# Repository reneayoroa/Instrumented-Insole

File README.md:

# Instrumented-Insole
KiCAD Design files for an instrumented insole

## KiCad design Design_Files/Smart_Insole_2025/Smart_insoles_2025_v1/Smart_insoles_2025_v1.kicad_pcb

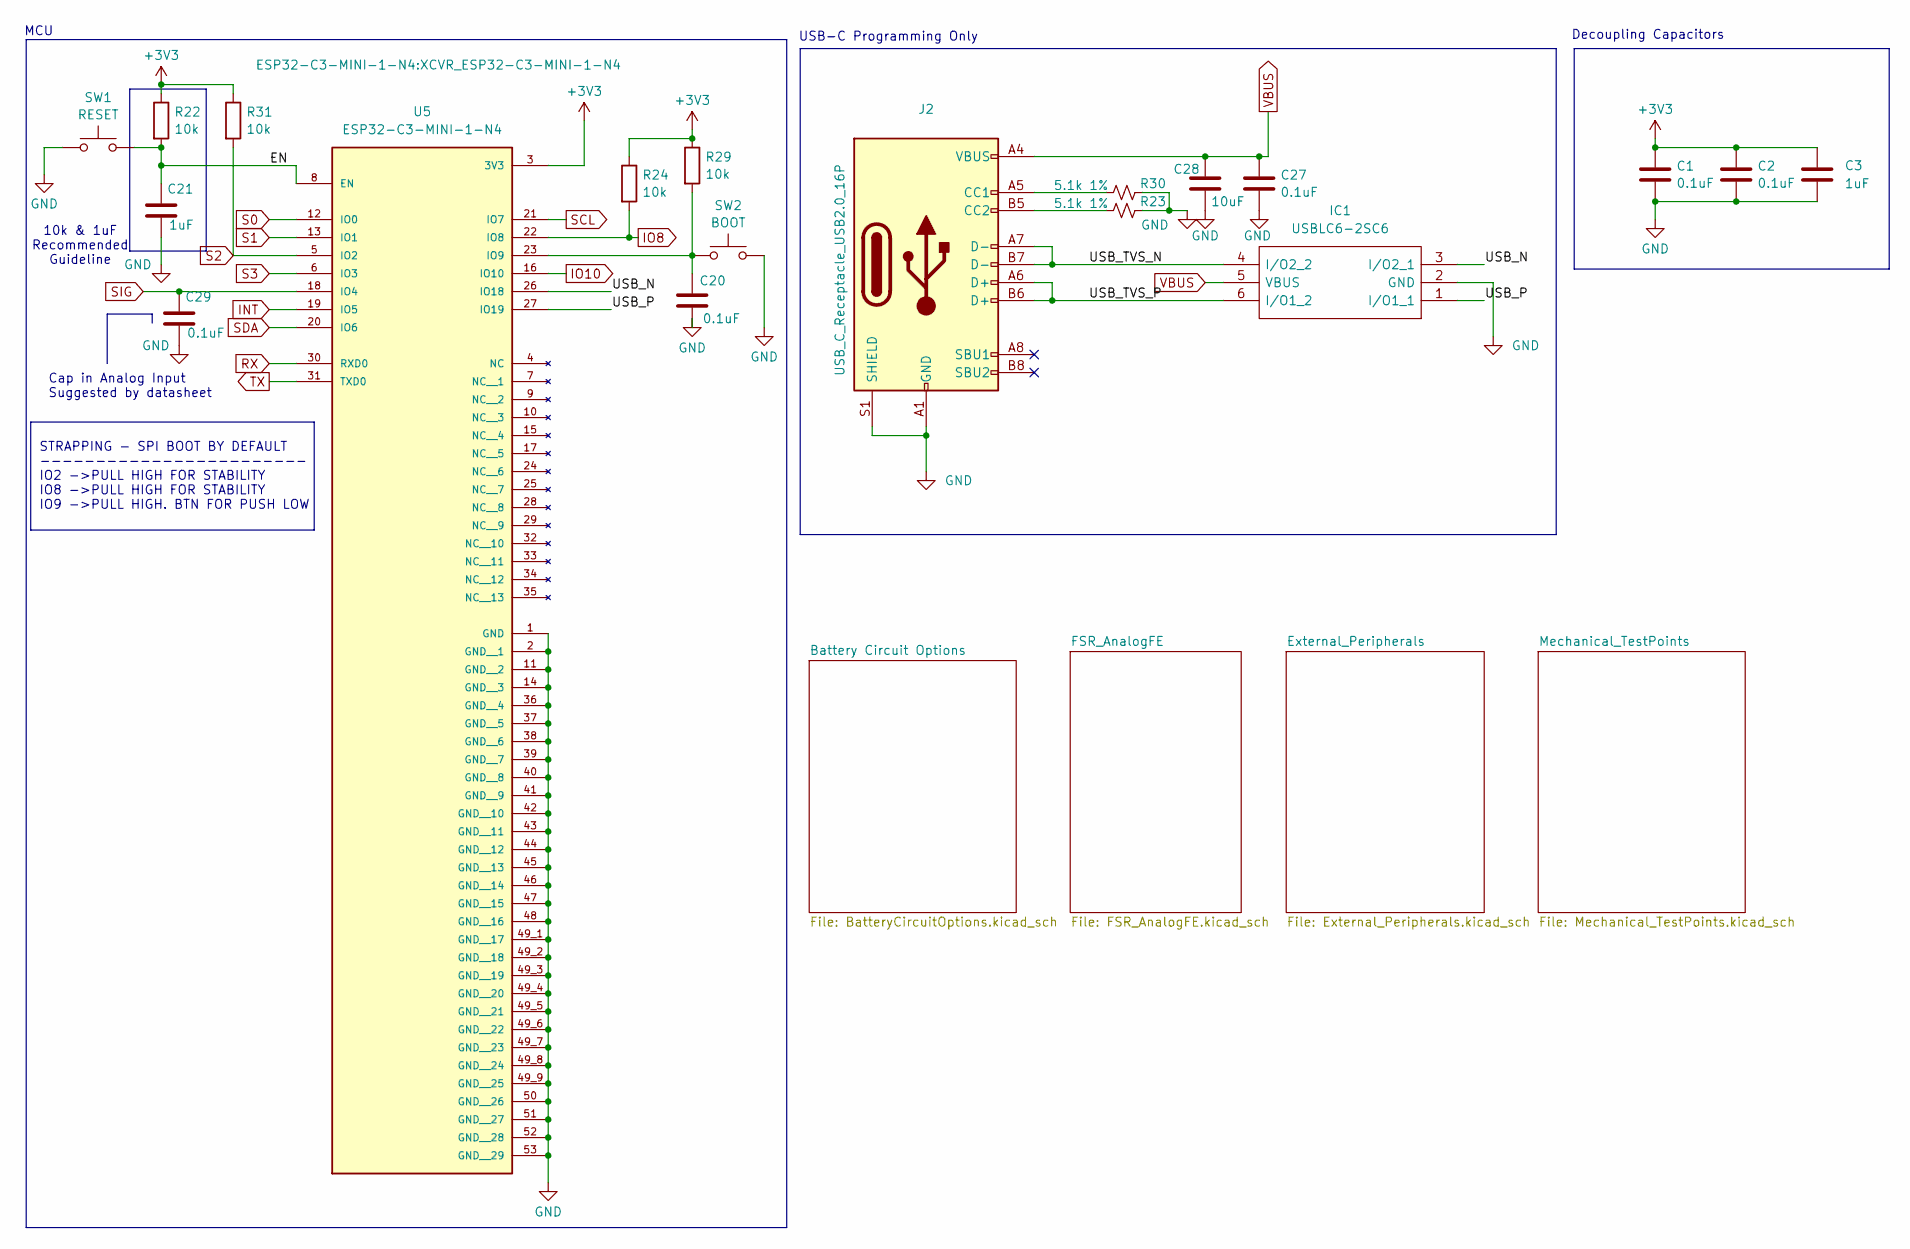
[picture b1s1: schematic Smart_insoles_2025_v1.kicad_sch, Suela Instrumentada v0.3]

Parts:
C1, C2, C20, C27, C29: 0.1uF; C_0805_2012Metric_Pad1.18x1.45mm_HandSolder
C3, C21: 1uF; C_0805_2012Metric_Pad1.18x1.45mm_HandSolder
C28: 10uF; C_0805_2012Metric_Pad1.18x1.45mm_HandSolder
IC1: USBLC6-2SC6; SOT95P280X145-6N; Mouser Part Number 511-USBLC6-2SC6
J2: USB_C_Receptacle_USB2.0_16P; USB_C_Receptacle_GCT_USB4105-xx-A_16P_TopMnt_Horizontal
R22, R24, R29, R31: 10k; R_0805_2012Metric
R23, R30: 5.1k 1%; R_0805_2012Metric
SW1: RESET; SW_Push_SPST_NO_Alps_SKRK
SW2: BOOT; SW_Push_SPST_NO_Alps_SKRK
U5: ESP32-C3-MINI-1-N4; XCVR_ESP32-C3-MINI-1-N4; PARTREV v1.0

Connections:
+3V3: C1.1, C2.1, C3.1, R22.1, R24.1, R29.1, R31.1, U5.3 (3V3); also elsewhere on the board
/EN: C21.2, R22.2, SW1.2, U5.8 (EN)
/USB_N: IC1.3 (I/O2_1), U5.26 (IO18)
/USB_P: IC1.1 (I/O1_1), U5.27 (IO19)
/USB_TVS_N: IC1.4 (I/O2_2), J2.A7 (D-), J2.B7 (D-)
/USB_TVS_P: IC1.6 (I/O1_2), J2.A6 (D+), J2.B6 (D+)
GND: C1.2, C2.2, C3.2, C20.1, C21.1, C27.2, C28.2, C29.1, IC1.2 (GND), J2.A1 (GND), J2.A12 (GND), J2.B1 (GND), J2.B12 (GND), J2.S1 (SHIELD), R23.2, R30.2, SW1.1, SW2.1, U5.1 (GND), U5.2 (GND__1), U5.11 (GND__2), U5.14 (GND__3), U5.36 (GND__4), U5.37 (GND__5), U5.38 (GND__6), U5.39 (GND__7), U5.40 (GND__8), U5.41 (GND__9), U5.42 (GND__10), U5.43 (GND__11), U5.44 (GND__12), U5.45 (GND__13), U5.46 (GND__14), U5.47 (GND__15), U5.48 (GND__16), U5.49_1 (GND__17), U5.49_2 (GND__18), U5.49_3 (GND__19), U5.49_4 (GND__20), U5.49_5 (GND__21), U5.49_6 (GND__22), U5.49_7 (GND__23), U5.49_8 (GND__24), U5.49_9 (GND__25), U5.50 (GND__26), U5.51 (GND__27), U5.52 (GND__28), U5.53 (GND__29); also elsewhere on the board
INT: U5.19 (IO5); also elsewhere on the board
IO8: R24.2, U5.22 (IO8); also elsewhere on the board
IO10: U5.16 (IO10); also elsewhere on the board
unnamed: J2.A5 (CC1), R30.1
unnamed: J2.B5 (CC2), R23.1
unnamed: C20.2, R29.2, SW2.2, U5.23 (IO9)
RX: U5.30 (RXD0); also elsewhere on the board
S0: U5.12 (IO0); also elsewhere on the board
S1: U5.13 (IO1); also elsewhere on the board
S2: R31.2, U5.5 (IO2); also elsewhere on the board
S3: U5.6 (IO3); also elsewhere on the board
SCL: U5.21 (IO7); also elsewhere on the board
SDA: U5.20 (IO6); also elsewhere on the board
SIG: C29.2, U5.18 (IO4); also elsewhere on the board
TX: U5.31 (TXD0); also elsewhere on the board
VBUS: C27.1, C28.1, IC1.5 (VBUS), J2.A4 (VBUS), J2.A9 (VBUS), J2.B4 (VBUS), J2.B9 (VBUS); also elsewhere on the board

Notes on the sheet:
USB-C Programming Only
STRAPPING - SPI BOOT BY DEFAULT ------------------------ IO2 ->PULL HIGH FOR STABILITY IO8 ->PULL HIGH FOR STABILITY IO9 ->PULL HIGH. BTN FOR PUSH LOW
MCU
10k & 1uF Recommended Guideline
Cap in Analog Input Suggested by datasheet
Decoupling Capacitors

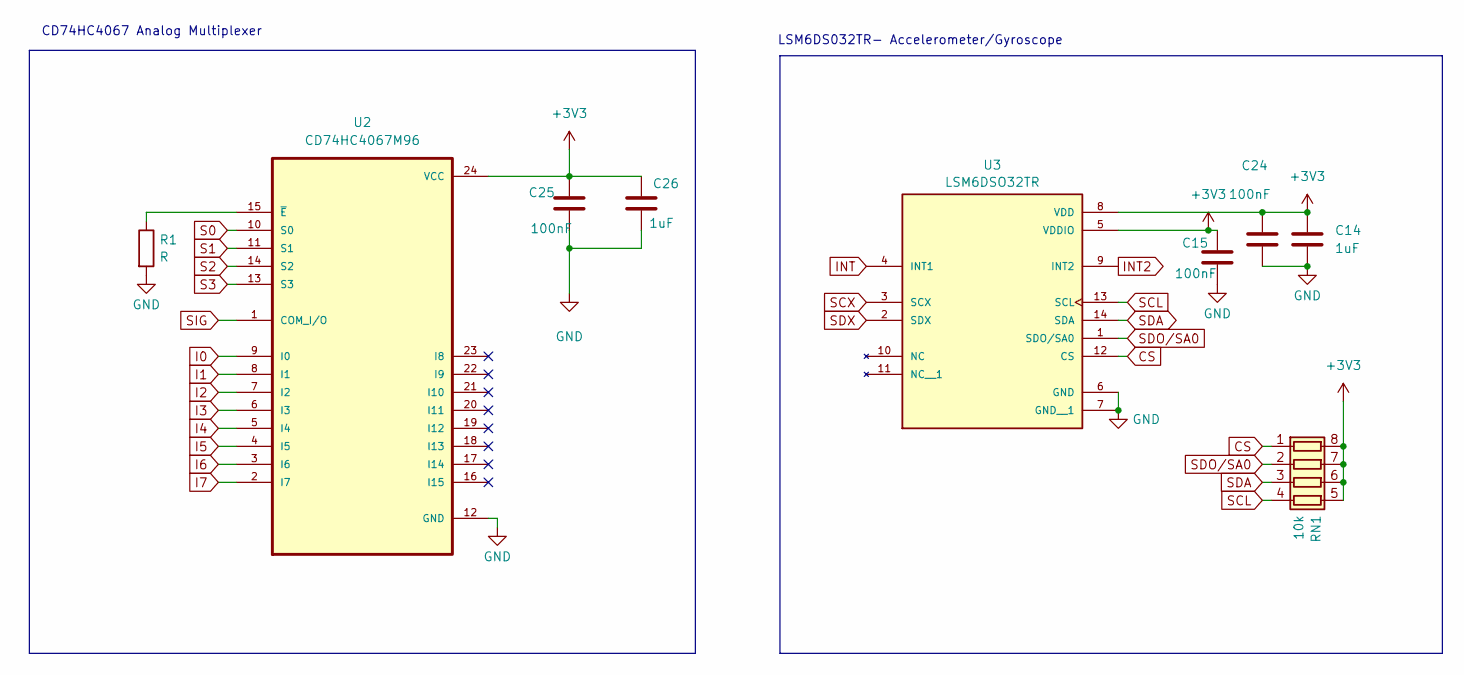
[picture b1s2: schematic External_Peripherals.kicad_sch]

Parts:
C14, C26: 1uF; C_0805_2012Metric_Pad1.18x1.45mm_HandSolder
C15, C24, C25: 100nF; C_0805_2012Metric_Pad1.18x1.45mm_HandSolder
R1: R; R_0805_2012Metric
RN1: 10k; R_Array_Concave_4x0603
U2: CD74HC4067M96; TSSOP-24_6.1x7.8mm_P0.65mm; DigiKey_Part_Number 296-29408-2-ND
U3: LSM6DSO32TR; XDCR_LSM6DSO32TR; PARTREV 1

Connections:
+3V3: C14.1, C15.1, C24.1, C25.1, C26.1, RN1.5 (R4.2), RN1.6 (R3.2), RN1.7 (R2.2), RN1.8 (R1.2), U2.24 (VCC), U3.5 (VDDIO), U3.8 (VDD); also elsewhere on the board
CS: RN1.1 (R1.1), U3.12 (CS)
GND: C14.2, C15.2, C24.2, C25.2, C26.2, R1.2, U2.12 (GND), U3.6 (GND), U3.7 (GND__1); also elsewhere on the board
I0: U2.9 (I0); also elsewhere on the board
I1: U2.8 (I1); also elsewhere on the board
I2: U2.7 (I2); also elsewhere on the board
I3: U2.6 (I3); also elsewhere on the board
I4: U2.5 (I4); also elsewhere on the board
I5: U2.4 (I5); also elsewhere on the board
I6: U2.3 (I6); also elsewhere on the board
I7: U2.2 (I7); also elsewhere on the board
INT: U3.4 (INT1); also elsewhere on the board
INT2: U3.9 (INT2); also elsewhere on the board
unnamed: R1.1, U2.15 (~E)
S0: U2.10 (S0); also elsewhere on the board
S1: U2.11 (S1); also elsewhere on the board
S2: U2.14 (S2); also elsewhere on the board
S3: U2.13 (S3); also elsewhere on the board
SCL: RN1.4 (R4.1), U3.13 (SCL); also elsewhere on the board
SCX: U3.3 (SCX); also elsewhere on the board
SDA: RN1.3 (R3.1), U3.14 (SDA); also elsewhere on the board
SDO/SA0: RN1.2 (R2.1), U3.1 (SDO/SA0); also elsewhere on the board
SDX: U3.2 (SDX); also elsewhere on the board
SIG: U2.1 (COM_I/O); also elsewhere on the board

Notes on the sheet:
LSM6DS032TR- Accelerometer/Gyroscope
CD74HC4067 Analog Multiplexer

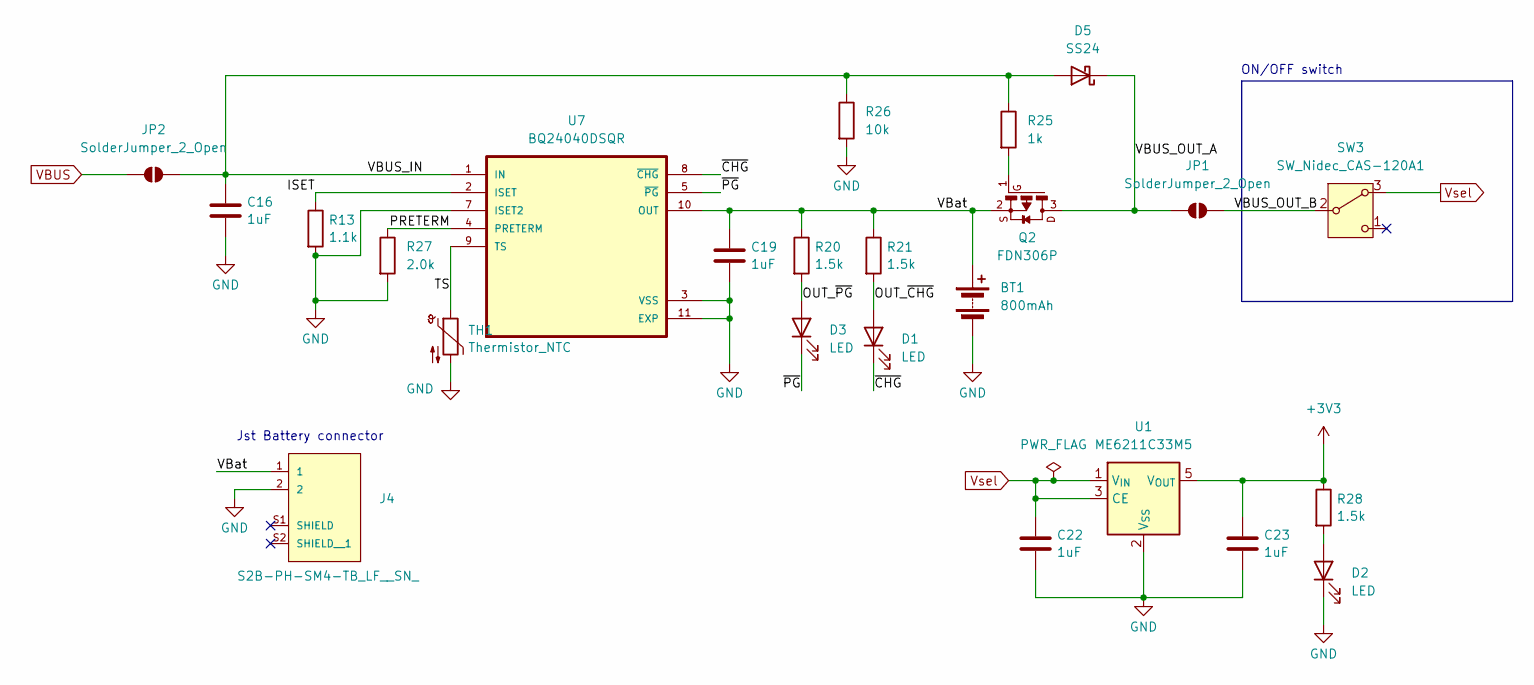
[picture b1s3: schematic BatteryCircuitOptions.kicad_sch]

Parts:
BT1: 800mAh
C16, C19, C22, C23: 1uF; C_0805_2012Metric_Pad1.18x1.45mm_HandSolder
D1, D2, D3: LED; LED_0805_2012Metric
D5: SS24; D_SMA
J4: S2B-PH-SM4-TB_LF__SN_; JST_S2B-PH-SM4-TB_LF__SN_
JP1, JP2: SolderJumper_2_Open; SolderJumper-2_P1.3mm_Open_RoundedPad1.0x1.5mm
Q2: FDN306P; SSOT-3
R13: 1.1k; R_0805_2012Metric_Pad1.20x1.40mm_HandSolder
R20, R21, R28: 1.5k; R_0805_2012Metric_Pad1.20x1.40mm_HandSolder
R25: 1k; R_0805_2012Metric_Pad1.20x1.40mm_HandSolder
R26: 10k; R_0805_2012Metric_Pad1.20x1.40mm_HandSolder
R27: 2.0k; R_0805_2012Metric_Pad1.20x1.40mm_HandSolder
SW3: SW_Nidec_CAS-120A1; SW_Slide-03_Wuerth-WS-SLTV_10x2.5x6.4_P2.54mm
TH1: Thermistor_NTC; thermistor_10k_NTC_SolderPad
U1: ME6211C33M5; SOT-23-5
U7: BQ24040DSQR; SON40P200X200X80-11N

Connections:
+3V3: C23.2, R28.1, U1.5 (V_{OUT}); also elsewhere on the board
/Battery Circuit Options/ISET: R13.1, U7.2 (ISET)
/Battery Circuit Options/OUT_~CHG: D1.2 (A), R21.2
/Battery Circuit Options/OUT_~PG: D3.2 (A), R20.2
/Battery Circuit Options/PRETERM: R27.1, U7.4 (PRETERM)
/Battery Circuit Options/TS: TH1.1, U7.9 (TS)
/Battery Circuit Options/VBUS_IN: C16.2, D5.2 (A), JP2.2 (B), R25.1, R26.1, U7.1 (IN)
/Battery Circuit Options/VBUS_OUT_A: D5.1 (K), JP1.1 (A), Q2.3
/Battery Circuit Options/VBUS_OUT_B: JP1.2 (B), SW3.2 (B)
/Battery Circuit Options/VBat: BT1.1 (+), C19.2, J4.1, Q2.2, R20.1, R21.1, U7.10 (OUT)
/Battery Circuit Options/~CHG: D1.1 (K), U7.8 (~CHG)
/Battery Circuit Options/~PG: D3.1 (K), U7.5 (~PG)
GND: BT1.2 (-), C16.1, C19.1, C22.1, C23.1, D2.1 (K), J4.2, R13.2, R26.2, R27.2, TH1.2, U1.2 (V_{SS}), U7.3 (VSS), U7.7 (ISET2), U7.11 (EXP); also elsewhere on the board
unnamed: D2.2 (A), R28.2
unnamed: Q2.1, R25.2
VBUS: JP2.1 (A); also elsewhere on the board
Vsel: C22.2, SW3.3 (A), U1.1 (V_{IN}), U1.3 (CE); also elsewhere on the board

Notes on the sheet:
ON/OFF switch
Jst Battery connector

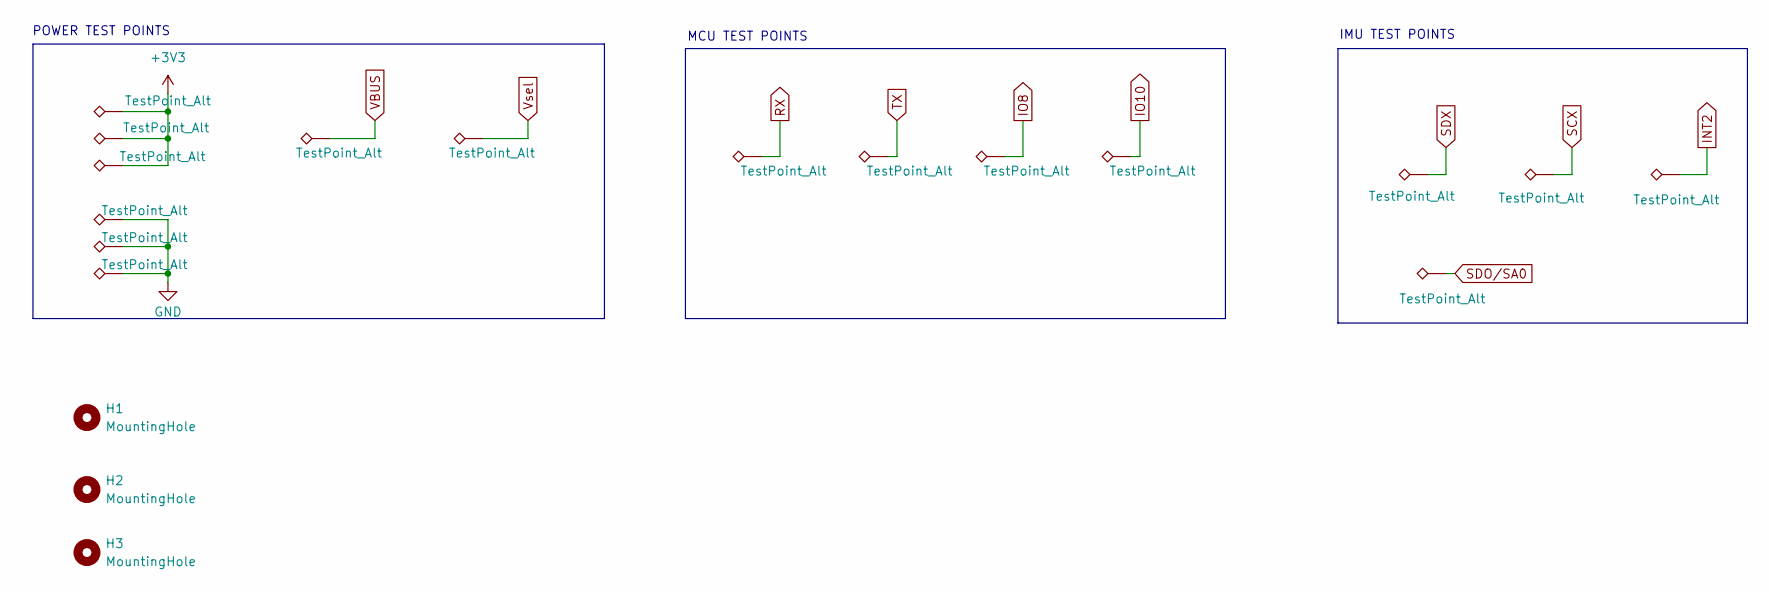
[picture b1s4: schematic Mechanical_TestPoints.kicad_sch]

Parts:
H1, H2, H3: MountingHole; MountingHole_2.1mm
TP1, TP2, TP3, TP4, TP5, TP6, TP7, TP8, TP9, TP10, TP11, TP12, TP13, TP14, TP15, TP16: TestPoint_Alt; TestPoint_Pad_D1.0mm

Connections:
+3V3: TP2.1, TP12.1, TP13.1; also elsewhere on the board
GND: TP1.1, TP15.1, TP16.1; also elsewhere on the board
INT2: TP11.1; also elsewhere on the board
IO8: TP7.1; also elsewhere on the board
IO10: TP8.1; also elsewhere on the board
RX: TP5.1; also elsewhere on the board
SCX: TP10.1; also elsewhere on the board
SDO/SA0: TP14.1; also elsewhere on the board
SDX: TP9.1; also elsewhere on the board
TX: TP6.1; also elsewhere on the board
VBUS: TP3.1; also elsewhere on the board
Vsel: TP4.1; also elsewhere on the board

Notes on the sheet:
POWER TEST POINTS
IMU TEST POINTS
MCU TEST POINTS

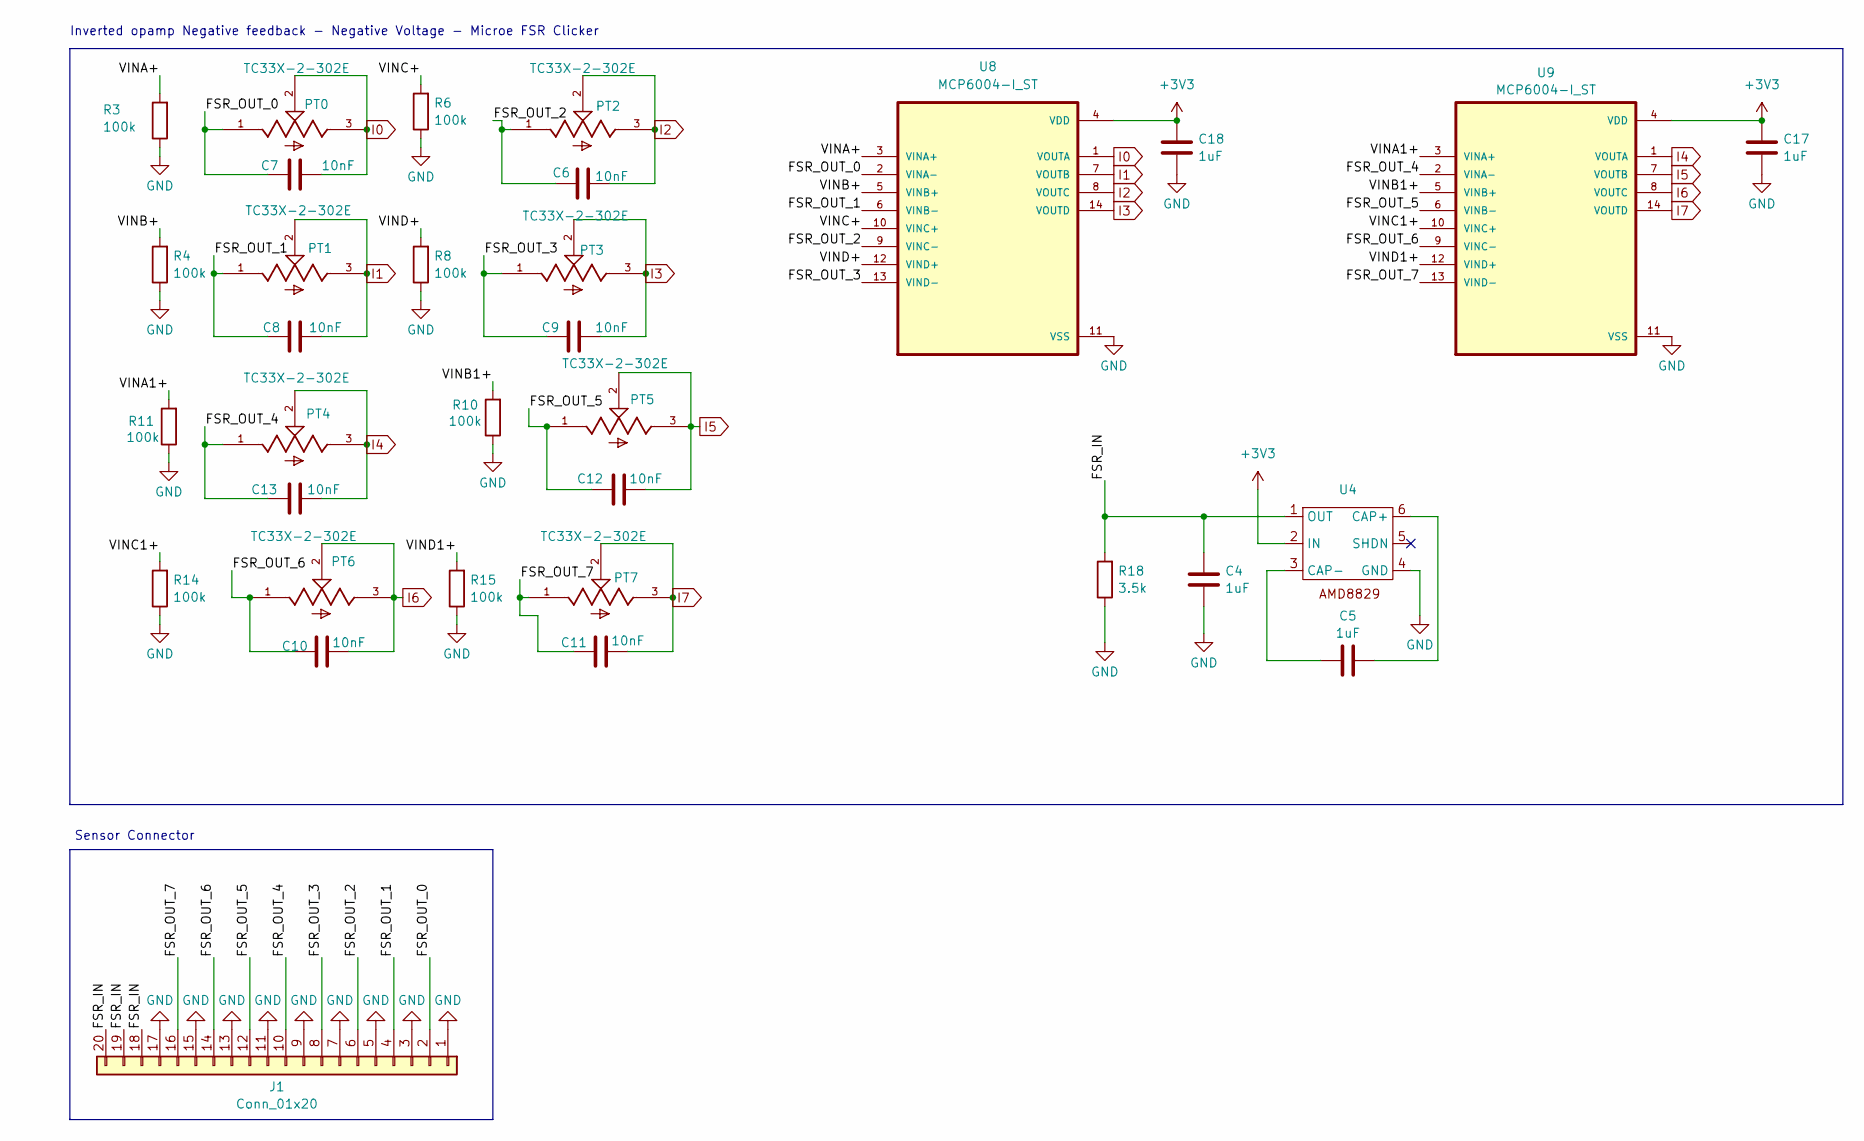
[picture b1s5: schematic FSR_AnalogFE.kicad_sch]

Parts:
C4, C5, C17, C18: 1uF; C_0805_2012Metric_Pad1.18x1.45mm_HandSolder
C6, C7, C8, C9, C10, C11, C12, C13: 10nF; C_0805_2012Metric_Pad1.18x1.45mm_HandSolder
J1: Conn_01x20; Samtec_T1M-20-X-S-RA_1x20-1MP_P1.0mm_Terminal_Horizontal
PT0, PT1, PT2, PT3, PT4, PT5, PT6, PT7: TC33X-2-302E; TRIM_TC33X-2-302E
R3, R4, R6, R10, R11, R14, R15: 100k; R_0805_2012Metric
R8: 100k; R_0805_2012Metric_Pad1.20x1.40mm_HandSolder
R18: 3.5k; R_0805_2012Metric
U4: SOT95P280X145-6N
U8, U9: MCP6004-I_ST; custom

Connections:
+3V3: C17.1, C18.1, U4.2 (IN), U8.4 (VDD), U9.4 (VDD); also elsewhere on the board
/FSR_AnalogFE/FSR_IN: C4.1, J1.18, J1.19, J1.20, R18.2, U4.1 (OUT)
/FSR_AnalogFE/FSR_OUT_0: C7.1, J1.2, PT0.1, U8.2 (VINA-)
/FSR_AnalogFE/FSR_OUT_1: C8.1, J1.4, PT1.1, U8.6 (VINB-)
/FSR_AnalogFE/FSR_OUT_2: C6.1, J1.6, PT2.1, U8.9 (VINC-)
/FSR_AnalogFE/FSR_OUT_3: C9.1, J1.8, PT3.1, U8.13 (VIND-)
/FSR_AnalogFE/FSR_OUT_4: C13.1, J1.10, PT4.1, U9.2 (VINA-)
/FSR_AnalogFE/FSR_OUT_5: C12.1, J1.12, PT5.1, U9.6 (VINB-)
/FSR_AnalogFE/FSR_OUT_6: C10.1, J1.14, PT6.1, U9.9 (VINC-)
/FSR_AnalogFE/FSR_OUT_7: C11.1, J1.16, PT7.1, U9.13 (VIND-)
/FSR_AnalogFE/VINA1+: R11.2, U9.3 (VINA+)
/FSR_AnalogFE/VINA+: R3.2, U8.3 (VINA+)
/FSR_AnalogFE/VINB1+: R10.2, U9.5 (VINB+)
/FSR_AnalogFE/VINB+: R4.2, U8.5 (VINB+)
/FSR_AnalogFE/VINC1+: R14.2, U9.10 (VINC+)
/FSR_AnalogFE/VINC+: R6.2, U8.10 (VINC+)
/FSR_AnalogFE/VIND1+: R15.2, U9.12 (VIND+)
/FSR_AnalogFE/VIND+: R8.2, U8.12 (VIND+)
GND: C4.2, C17.2, C18.2, J1.1, J1.3, J1.5, J1.7, J1.9, J1.11, J1.13, J1.15, J1.17, R3.1, R4.1, R6.1, R8.1, R10.1, R11.1, R14.1, R15.1, R18.1, U4.4 (GND), U8.11 (VSS), U9.11 (VSS); also elsewhere on the board
I0: C7.2, PT0.2, PT0.3, U8.1 (VOUTA); also elsewhere on the board
I1: C8.2, PT1.2, PT1.3, U8.7 (VOUTB); also elsewhere on the board
I2: C6.2, PT2.2, PT2.3, U8.8 (VOUTC); also elsewhere on the board
I3: C9.2, PT3.2, PT3.3, U8.14 (VOUTD); also elsewhere on the board
I4: C13.2, PT4.2, PT4.3, U9.1 (VOUTA); also elsewhere on the board
I5: C12.2, PT5.2, PT5.3, U9.7 (VOUTB); also elsewhere on the board
I6: C10.2, PT6.2, PT6.3, U9.8 (VOUTC); also elsewhere on the board
I7: C11.2, PT7.2, PT7.3, U9.14 (VOUTD); also elsewhere on the board
unnamed: C5.2, U4.6 (CAP+)
unnamed: C5.1, U4.3 (CAP-)

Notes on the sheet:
Inverted opamp Negative feedback - Negative Voltage - Microe FSR Clicker
Sensor Connector

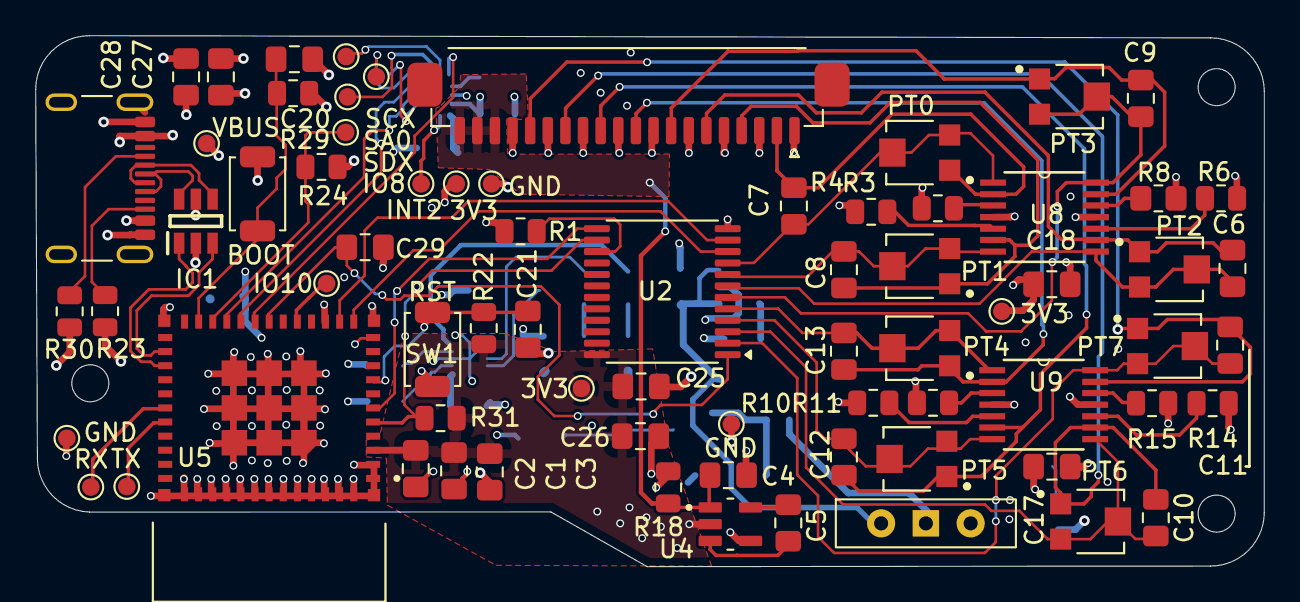
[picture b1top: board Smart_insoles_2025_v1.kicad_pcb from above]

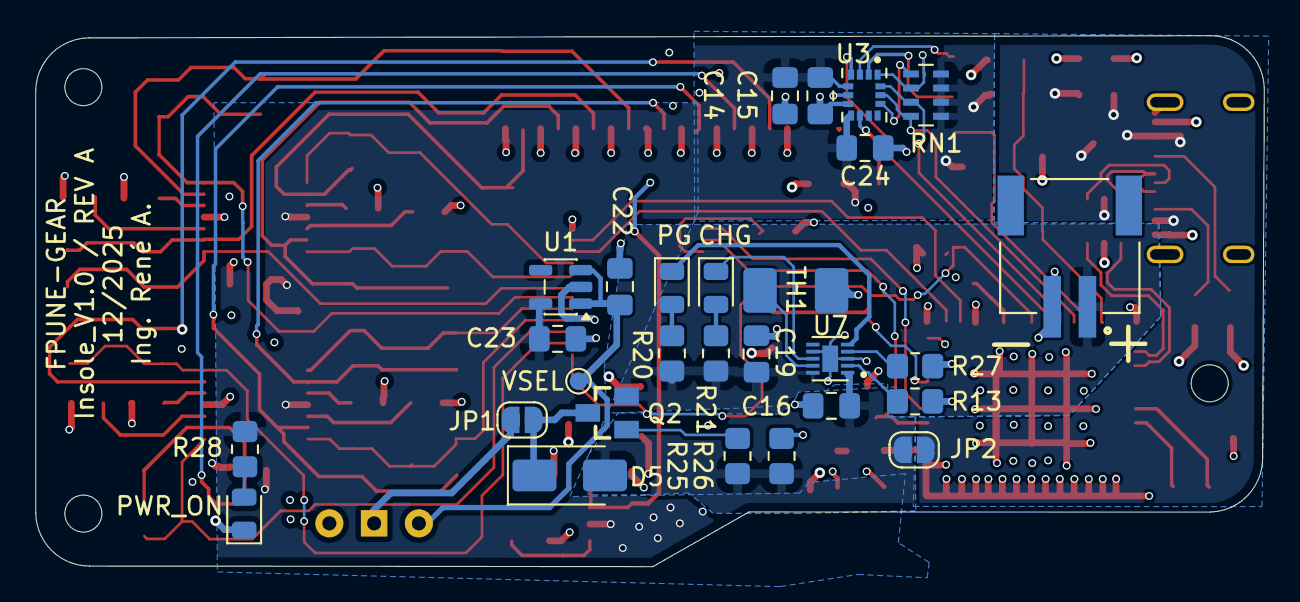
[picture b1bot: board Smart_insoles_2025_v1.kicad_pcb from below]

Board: 4 copper layers, 69.7 x 30.1 mm, 103 parts (28 on the bottom side), 70 nets.

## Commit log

2025-06-20 updated Schematic & PCB layout
2025-06-21 Changing MCU orientation + Rerouting
2025-07-01 modified project outline and routing.
2025-07-16 Added AFE from mikroe clicker schematic. Reorganized Schematic in general
2025-07-19 Added different AFE circuits to the schematic. Needs verification
2025-07-23 Added capacitor to negative feedback fsr circuit
2025-08-19 Project division to account for multiple AFE conditioning circuit
2025-08-20 added 3x3 trimpot symbol/footprint. Also Modify schematic to add 3x3trimpots
2025-08-21 Added capacitors to the AFE
2025-08-26 Change accelerometer to Lsm6ds033
2025-08-27 Added battery connector footprint. Grouping componnets in PcbNew
2025-09-04 PCBNew. AFE component grouping
2025-09-05 PCBnew:Moving placed components. Fixed REF of mcp component
2025-09-10 PCB new moving things around
2025-09-19 Changed Mcu to esp32c3 mini 1 n4
2025-09-23 SCH: Advances in Battery circuit. Added External_Periph sheet
2025-09-24 SCH: Added TVS diode on USB. Defined transistor and diode for battery/usb charging/switching
2025-09-24 SCH:Solved Errors in ERC
2025-09-25 SCH: Added missing footprints. PCB: Grouped related components for new layout
2025-09-27 SCH: Fixed Warnings. Added thermistor solder pads library.
2025-09-27 SCH: Added Power Test points and Mounting Holes. PCB: Arranged grouped Footprints to minimize rounting
2025-09-27 SCH: Added FSR_In missing connections.
2025-09-28 PCB:Initial positioning of grouped footprints
2025-09-30 SCH: Added test points on idle MCU pins and Power supply. Added ON/OFF switch on VSEL.
2025-10-01 PCB: Added 3d models to all components. Also preliminar routing of componentes. Component placemente needs checking.
2025-10-15 PCB:Routing missing connection. Still some missing
2025-11-12 PCB:new routing-p1
2025-11-13 PCB: finished routing single ended signal. Pending usb differential pair
2025-11-27 SCH:Added pullup resistors on strapping pins.Added 0.1uF on analog input. Added testpoint on missing pad. PCB:Placed new components.Routing refactoring p1
2025-12-01 PCB: Routing refactoring. Moved Multiplexer to the right. Organized Silkscreen p1. USB DIFF NOT READY
2025-12-03 PCB: Added power puddles on Vbat,3v3, VBUS
2025-12-04 PCB:USB Differential pair Impedance calculation and Routing. Also Organized Silkscreen. Added text polarity to battery, boot and rst buttons, and RX TX
2025-12-04 PCB:Fixed Multiplexer wrong footprint. Flex Connector modified. Fixed DRC Errors and Warnings
2025-12-04 Modified some footprints to better fit real components.
2025-12-06 PCB: Changed USB position. VERSION SENT TO JLCPCB
